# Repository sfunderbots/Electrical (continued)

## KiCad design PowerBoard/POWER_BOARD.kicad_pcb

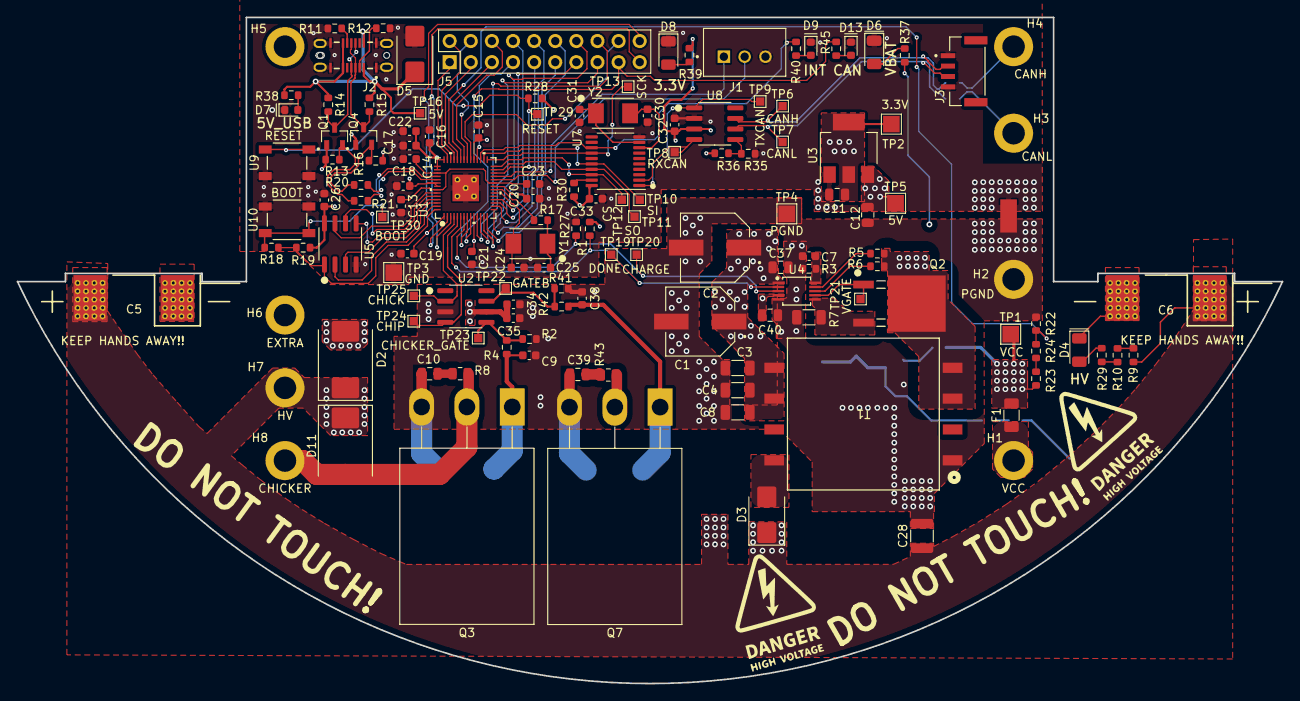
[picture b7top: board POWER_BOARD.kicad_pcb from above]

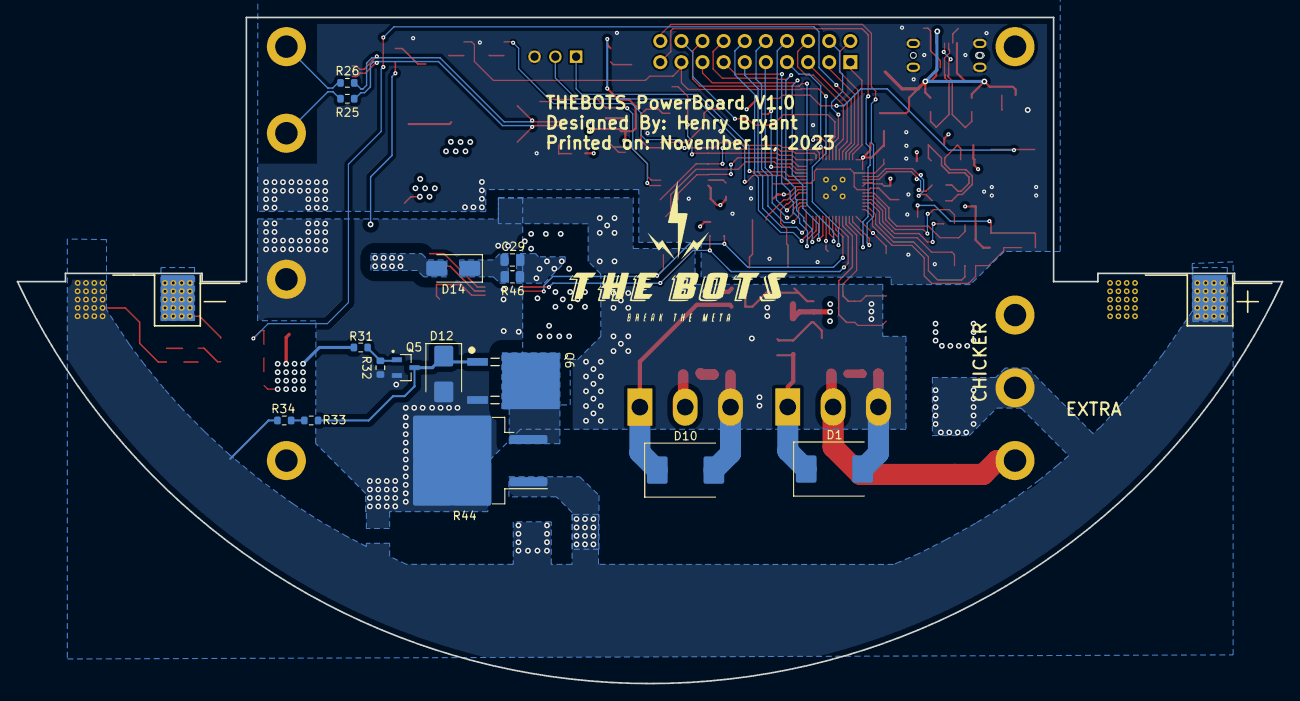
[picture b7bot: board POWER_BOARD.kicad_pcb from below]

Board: 4 copper layers, 152.1 x 80.1 mm, 154 parts (15 on the bottom side), 99 nets.

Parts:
C1, C2: 25SVPF100M; CAP_25SVPF100M
C3, C4, C8: C_22u_1206; C_1206_3216Metric
C5: 1000u; CP_Radial_Horizontal_D25.4mm_H45mm
C6: 1000u; CP_Radial_Horizontal_D25.4mm_H45mm_reversed
C7: 100p; C_0603_1608Metric
C9, C13, C14, C15, C16, C17, C18, C19, C20, C21, C26, C32, C33, C34, C38: 0.1u; C_0603_1608Metric
C10, C39: 1500p; C_0805_2012Metric
C11, C12: 10u; C_0805_2012Metric
C22, C23, C35: 1u; C_0603_1608Metric
C24, C25: 27p; C_0603_1608Metric
C28: 0.1u_600V; C_1210_3225Metric
C29: ?; C_0805_2012Metric
C30, C31: 22p; C_0603_1608Metric
C37, C40: C_10u; C_0805_2012Metric
D1, D10: SMCJ14A; D_SMC
D2, D11: MUR860J; D_SMC
D3: 2A 600V; D_SMB
D4: LED_red; LED_1206_3216Metric
D5: B220; D_SMB
D6, D8: LED; LED_1206_3216Metric
D7, D9, D13: LED; LED_0603_1608Metric
D12: 3SMBJ5929B-TP; D_SMB
D14: ?; D_SMA
F1: Fuse_0501010.WR; Fuse_1206_3216Metric
H1: VCC; MountingHole_2.7mm_M2.5_DIN965_Pad
H2: PGND; MountingHole_2.7mm_M2.5_DIN965_Pad
H3: CANL; MountingHole_2.7mm_M2.5_DIN965_Pad
H4: CANH; MountingHole_2.7mm_M2.5_DIN965_Pad
H5: 5V; MountingHole_2.7mm_M2.5_DIN965_Pad
H6: EXTRA; MountingHole_2.7mm_M2.5_DIN965_Pad
H7: HV; MountingHole_2.7mm_M2.5_DIN965_Pad
H8: CHICKER; MountingHole_2.7mm_M2.5_DIN965_Pad
J1: JST_B3B-XH-A
J2: USB4145-03-0170-C_REVA2; GCT_USB4145-03-0170-C_REVA2
J3: JST_BM04B-GHS-TBT
J5: Conn_02x10_Counter_Clockwise; PinHeader_2x10_P2.54mm_Vertical
NT1: NetTie_2; NetTie-2_SMD_Pad2.0mm
Q1, Q4: BSS138; SOT95P240X111-3N
Q2: FDD86250-F085; DPAK-3_ONS
Q3, Q7: FGH50T65SQD-F155; TO-247-3_Horizontal_TabDown
Q5: TN2130K1-G; SOT95P240X111-3N
Q6: STD11N60DM2; DPAK-3_ONS
R1, R9, R10, R27, R29, R32: 100k; R_0603_1608Metric
R2, R13, R14, R15, R16, R19, R28, R30, R41: 10k; R_0603_1608Metric
R3: 2.49k; R_0603_1608Metric
R4, R42: 110; R_0603_1608Metric
R5: 48.1k; R_0603_1608Metric
R6: 34.3k; R_0603_1608Metric
R7: 8m; R_1206_3216Metric
R8, R43: 2; R_0805_2012Metric
R11, R12, R35, R36: 5.1k; R_0603_1608Metric
R17, R18: 1k; R_0603_1608Metric
R20, R21: 27.4; R_0603_1608Metric
R22: R_200k; R_0603_1608Metric
R23, R24: R_470k; R_0603_1608Metric
R25, R26: R_0OHM_JUMPER; R_0603_1608Metric
R31: 270k; R_0603_1608Metric
R33, R34: 5.1M; R_0603_1608Metric
R37: 3k; R_0603_1608Metric
R38, R39, R40, R45: 330; R_0603_1608Metric
R44: 1k 50W; TO-263-2
R46: ?; R_0805_2012Metric
T1: 750032050; SMT_32050_WRE
TP1: VCC; TestPoint_Pad_2.0x2.0mm
TP2: 3.3V; TestPoint_Pad_2.0x2.0mm
TP3: GND; TestPoint_Pad_2.0x2.0mm
TP4: PGND; TestPoint_Pad_2.0x2.0mm
TP5: 5V; TestPoint_Pad_2.0x2.0mm
TP6: CANH; TestPoint_Pad_1.0x1.0mm
TP7: CANL; TestPoint_Pad_1.0x1.0mm
TP8: RXCAN; TestPoint_Pad_1.0x1.0mm
TP9: TXCAN; TestPoint_Pad_1.0x1.0mm
TP10: SI; TestPoint_Pad_1.0x1.0mm
TP11: SO; TestPoint_Pad_1.0x1.0mm
TP12: CS; TestPoint_Pad_1.0x1.0mm
TP13: SCK; TestPoint_Pad_1.0x1.0mm
TP16: 5V; TestPoint_Pad_1.0x1.0mm
TP19: DONE; TestPoint_Pad_1.0x1.0mm
TP20: CHARGE; TestPoint_Pad_1.0x1.0mm
TP21: VGATE; TestPoint_Pad_1.0x1.0mm
TP22: GATEB; TestPoint_Pad_1.0x1.0mm
TP23: CHICKER_GATE; TestPoint_Pad_1.0x1.0mm
TP24: CHIP; TestPoint_Pad_1.0x1.0mm
TP25: CHICK; TestPoint_Pad_1.0x1.0mm
TP29: RESET; TestPoint_Pad_1.0x1.0mm
TP30: BOOT; TestPoint_Pad_1.0x1.0mm
U1: RPI2040; QFN56_7X7_RPI
U2: MCP14A0454-E/SN; SOIC-8_3.9x4.9mm_P1.27mm
U3: AP2114HA-3.3TRG1; SOT-223-3_TabPin2
U4: LT3750; MSOP-10_3x3mm_P0.5mm
U5: W25Q16JVSNIQ; SOIC-8_3.9x4.9mm_P1.27mm
U7: MCP2515-xST; TSSOP-20_4.4x6.5mm_P0.65mm
U8: MCP2551-I-SN; SOIC-8_3.9x4.9mm_P1.27mm
U9, U10: PTS647SM38SMTR2LFS; SW_PTS647SM38SMTR2LFS_CNK
Y1: ABM3-12.000MHZ-D2Y-T; ABM3
Y2: ABM3-8.000MHZ-D2Y-T; ABM3

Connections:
5V_USB: D5.1 (K), J2.A4 (VBUS_A), J2.A9 (VBUS_A), J2.B4 (VBUS_B), J2.B9 (VBUS_B), R14.1, R15.1, R38.2, TP16.1
+3.3V: C11.1, C15.1, C16.1, C17.1, C18.1, C19.1, C20.1, C21.1, C22.1, C26.1, C32.1, C33.1, Q1.1, Q4.1, R1.2, R13.1, R16.1, R19.2, R28.1, R30.1, R36.1, R39.2, TP2.1, U1.1 (IOVDD), U1.10 (IOVDD), U1.22 (IOVDD), U1.33 (IOVDD), U1.42 (IOVDD), U1.43 (ADC_AVDD), U1.44 (VREG_VIN), U1.48 (USB_VDD), U1.49 (IOVDD), U3.2 (OUTPUT), U5.8 (VCC), U7.20 (VDD), U8.3 (VDD)
+5V: C12.1, H5.1, TP5.1, U3.3 (INPUT)
/Flyback_HV/AD_50W: Q6.2 (D), R44.3
/Flyback_HV/AD_G: D12.1 (K), Q5.3, Q6.1 (G), R33.2
/Flyback_HV/AD_LV_G: Q5.1, R31.2, R32.1
/Flyback_HV/AD_R: R33.1, R34.2
/Flyback_HV/CHICKER_GATE: R2.1, R4.2, TP23.1, U2.5 (OUTA)
/Flyback_HV/EXTRA_GATE: R41.1, R42.2, TP22.1, U2.7 (OUTB)
/Flyback_HV/HV_DIO: D3.2 (A), T1.8 (Vout)
/Flyback_HV/IGBTGATE_CHICKER: C9.1, D1.1 (K), Q3.1 (G), R4.1
/Flyback_HV/IGBTGATE_EXTRA: C38.1, D10.1 (K), Q7.1 (G), R42.1
/Flyback_HV/Q2D: D14.2 (A), Q2.2 (D), R5.2, R6.2, T1.3 (VinCOM2), T1.4 (VinCOM3)
/Flyback_HV/RBG: C7.1, R3.2, U4.10 (RBG)
/Flyback_HV/RCD: C29.2, D14.1 (K), R46.2
/Flyback_HV/RDCM: R6.1, U4.8 (RDCM)
/Flyback_HV/RVOUT: R5.1, U4.9 (RVOUT)
/Flyback_HV/SNUB: C39.1, R43.2
/Flyback_HV/SNUB2: C10.1, R8.2
/Flyback_HV/VSOURCE: Q2.3 (S), R7.2, U4.6 (SOURCE)
/Power/3V3_DIO: D8.2 (A), R39.1
/Power/CANR+: H4.1, R26.1
/Power/CANR-: H3.1, R25.1
/Power/USB_DIO: D7.2 (A), R38.1
/Power/VCC_DIO: D6.2 (A), R37.1
/Power/VCC_FUSE: F1.1, H1.1
/RP2040_CAN_FLASH/+1.1V: C13.1, C14.1, C23.1, U1.23 (DVDD), U1.45 (VREG_VOUT), U1.50 (DVDD)
/RP2040_CAN_FLASH/BOOT: R18.1, TP30.1, U10.1, U10.2
/RP2040_CAN_FLASH/CC1: J2.A5 (CC1), R12.1
/RP2040_CAN_FLASH/CC2: J2.B5 (CC2), R11.1
/RP2040_CAN_FLASH/D+: Q4.2, R16.2, R20.2
/RP2040_CAN_FLASH/D-: Q1.2, R13.2, R21.2
/RP2040_CAN_FLASH/DR+: R20.1, U1.47 (USB_DP)
/RP2040_CAN_FLASH/DR-: R21.1, U1.46 (USB_DM)
/RP2040_CAN_FLASH/Data+: J2.A6 (DP1), J2.B6 (DP2), Q4.3, R15.2
/RP2040_CAN_FLASH/Data-: J2.A7 (DN1), J2.B7 (DN2), Q1.3, R14.2
/RP2040_CAN_FLASH/GPIO6: J5.17, R45.1, U1.8 (GPIO6)
/RP2040_CAN_FLASH/GPIO7: J5.16, U1.9 (GPIO7)
/RP2040_CAN_FLASH/GPIO8: J5.15, U1.11 (GPIO8)
/RP2040_CAN_FLASH/GPIO9: J5.14, U1.12 (GPIO9)
/RP2040_CAN_FLASH/GPIO10: J5.13, U1.13 (GPIO10)
/RP2040_CAN_FLASH/GPIO11: J5.12, U1.14 (GPIO11)
/RP2040_CAN_FLASH/GPIO12: J5.11, U1.15 (GPIO12)
/RP2040_CAN_FLASH/GPIO13: J5.10, U1.16 (GPIO13)
/RP2040_CAN_FLASH/GPIO14: J5.9, U1.17 (GPIO14)
/RP2040_CAN_FLASH/GPIO15: J5.8, U1.18 (GPIO15)
/RP2040_CAN_FLASH/GPIO21: J5.7, U1.32 (GPIO21)
/RP2040_CAN_FLASH/GPIO22: J5.18, U1.34 (GPIO22)
/RP2040_CAN_FLASH/GPIO23: J5.4, U1.35 (GPIO23)
/RP2040_CAN_FLASH/GPIO24: J5.6, U1.36 (GPIO24)
/RP2040_CAN_FLASH/GPIO25: J5.5, U1.37 (GPIO25)
/RP2040_CAN_FLASH/GPIO27_ADC1: J5.3, U1.39 (GPIO27/ADC1)
/RP2040_CAN_FLASH/GPIO28_ADC2: J5.2, U1.40 (GPIO28/ADC2)
/RP2040_CAN_FLASH/GPIO29_ADC3: J5.1, U1.41 (GPIO29/ADC3)
/RP2040_CAN_FLASH/INT: R40.1, U1.31 (GPIO20), U7.13 (~INT)
/RP2040_CAN_FLASH/OSC1: C31.1, U7.9 (OSC1), Y2.1
/RP2040_CAN_FLASH/OSC2: C30.1, U7.8 (OSC2), Y2.2
/RP2040_CAN_FLASH/QSPI_SCLK: U1.52 (SQPI_SCLK), U5.6 (CLK)
/RP2040_CAN_FLASH/QSPI_SD0: U1.53 (SQPI_SD0), U5.5 (DI(IO0))
/RP2040_CAN_FLASH/QSPI_SD1: U1.55 (SQPI_SD1), U5.2 (DO(IO1))
/RP2040_CAN_FLASH/QSPI_SD2: U1.54 (SQPI_SD2), U5.3 (IO2)
/RP2040_CAN_FLASH/QSPI_SD3: U1.51 (SQPI_SD3), U5.7 (IO3)
/RP2040_CAN_FLASH/QSPI_SS: R18.2, R19.1, U1.56 (SQPI_SS_N), U5.1 (~CS)
/RP2040_CAN_FLASH/RUN: R28.2, TP29.1, U1.26 (RUN), U9.1, U9.2
/RP2040_CAN_FLASH/RX: J5.20, U1.2 (GPIO0)
/RP2040_CAN_FLASH/RXCAN: TP8.1, U7.2 (RXCAN), U8.4 (RXD)
/RP2040_CAN_FLASH/SPI0_CS: TP12.1, U1.28 (GPIO17), U7.18 (~CS)
/RP2040_CAN_FLASH/SPI0_RX: TP11.1, U1.27 (GPIO16), U7.17 (SO)
/RP2040_CAN_FLASH/SPI0_SCK: TP13.1, U1.29 (GPIO18), U7.14 (SCK)
/RP2040_CAN_FLASH/SPI0_TX: TP10.1, U1.30 (GPIO19), U7.16 (SI)
/RP2040_CAN_FLASH/SWCLK: J1.2, U1.24 (SWCLK)
/RP2040_CAN_FLASH/SWDIO: J1.1, U1.25 (SWDIO)
/RP2040_CAN_FLASH/TX: J5.19, U1.3 (GPIO1)
/RP2040_CAN_FLASH/TXCAN: TP9.1, U7.1 (TXCAN), U8.1 (TXD)
/RP2040_CAN_FLASH/Vref1.65V: R35.1, R36.2, U8.5 (Vref)
/RP2040_CAN_FLASH/XIN: C24.2, U1.20 (XIN), Y1.2
/RP2040_CAN_FLASH/XOUT: R17.2, U1.21 (XOUT)
BATT_LEVEL: R22.1, R24.2, U1.38 (GPIO26/ADC0)
CAN+: J3.2, R26.2, TP6.1, U8.7 (CANH)
CAN-: J3.3, R25.2, TP7.1, U8.6 (CANL)
CHARGE: R27.1, TP20.1, U1.7 (GPIO5), U4.3 (CHARGE)
CHICKER: TP25.1, U1.4 (GPIO2), U2.2 (INA)
CHICKER_HV: D11.2 (A), H8.1, Q3.2 (C), R8.1
CHIP_EXTRA: TP24.1, U1.5 (GPIO3), U2.4 (INB)
DONE: R1.1, TP19.1, U1.6 (GPIO4), U4.2 (~DONE)
EXTRA_HV: D2.2 (A), H6.1, Q7.2 (C), R43.1
GND: C11.2, C13.2, C14.2, C15.2, C16.2, C17.2, C18.2, C19.2, C20.2, C21.2, C22.2, C23.2, C24.1, C25.1, C26.2, C30.2, C31.2, C32.2, C33.2, D5.2 (A), D6.1 (K), D7.1 (K), D8.1 (K), D9.1 (K), D13.1 (K), J1.3, J2.A1 (GND_A), J2.A12 (GND_A), J2.B1 (GND_B), J2.B12 (GND_B), J2.S1 (SHIELD), J2.S2 (SHIELD), J2.S3 (SHIELD), J2.S4 (SHIELD), J3.1, J3.4, NT1.2, R11.2, R12.2, R27.2, R35.2, TP3.1, U1.19 (TESTEN), U1.57 (GND), U3.1 (GND), U5.4 (GND), U7.10 (VSS), U8.2 (VSS), U9.3, U9.4, U10.3, U10.4
GNDPWR: C1.2, C2.2, C3.2, C4.2, C5.2, C6.2, C7.2, C8.2, C9.2, C10.2, C12.2, C28.2, C34.2, C35.2, C37.2, C38.2, C39.2, C40.2, D1.2 (A), D4.1 (K), D10.2 (A), D12.2 (A), H2.1, NT1.1, Q3.3 (E), Q5.2, Q6.3 (S), Q7.3 (E), R2.2, R3.1, R7.1, R22.2, R32.2, R41.2, R44.2, T1.1 (VoutCOM), TP4.1, U2.3 (GND), U4.5 (GND)
HV: C5.1, C6.1, C28.1, D2.1 (K), D3.1 (K), D11.1 (K), H7.1, R9.2, R34.1, R44.1
unnamed: C25.2, R17.1, Y1.1
unnamed: D4.2 (A), R29.1
unnamed: D9.2 (A), R40.2
unnamed: D13.2 (A), R45.2
unnamed: Q2.1 (G), TP21.1, U4.7 (GATE)
unnamed: R10.1, R29.2
unnamed: R9.1, R10.2
unnamed: R23.2, R24.1
unnamed: R30.2, U7.19 (~RESET)
VCC: C1.1, C2.1, C3.1, C4.1, C8.1, C29.1, C34.1, C35.1, C37.1, C40.1, F1.2, R23.1, R31.1, R37.2, R46.1, T1.5 (Vin1), T1.6 (Vin2), TP1.1, U2.6 (VDD), U4.1 (VTRANS), U4.4 (VCC)

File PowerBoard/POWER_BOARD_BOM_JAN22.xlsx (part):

Reference | Value | Footprint | JLC Extended | MPN | JLC Part # | Digikey cost 1 unit | Digikey Cost 10 units | JLC Cost | Layer | DNP QTY | Qty per board | QTY after DNP | QTY Have | QTY need if Digikey | QTY digikey order | QTY to solder digikey | QTY *10 + spare for JLC | Digikey Cost (total) | JLC Cost with Extended part fee (total) | Override | Lowest Cost (Digikey vs JLC)
C1, C2 | 25SVPF100M | bots:CAP_25SVPF100M | yes | 25SVPF100M | C136279 | 1.97000 | 1.4710000000000001 | 1.0630500000000001 |  |  | 2 | 2 |  | 20 | 0 | 0 | 20 | 29.42 | 25.301000000000002 |  | 25.301000000000002 | JLC
C3, C4, C8 | 22u_1206 | bots:C_1206_3216Metric | no | CL31A226KAHNNNE | C12891 | 0.51000 | 0.33800000000000002 | 6.4500000000000002E-2 |  |  | 3 | 3 |  | 30 | 0 | 24 | 30 | 10.14 | 1.9350000000000001 |  | 1.9350000000000001 | JLC
C5, C6 | 1000u | bots:CP_Radial_Horizontal_D25.4mm_H45mm |  | ESMQ251VSN102MQ45S |  | 8.76000 | 7.53 |  |  |  | 2 | 2 | 8 | 8 | 8 | 16 | 12 | 70.08 | EMPTY |  | 70.08 | DIGIKEY
C7 | 100p | bots:C_0603_1608Metric | no | CL10C101JB8NNNC | C14858 | 0.14000 | 3.6999999999999998E-2 | 2.5999999999999999E-3 |  |  | 1 | 1 |  | 10 | 0 | 8 | 10 | 0.37 | 2.5999999999999999E-2 |  | 2.5999999999999999E-2 | JLC
C9, C13-C21, C26, C32-C34, C38 | 0.1u | bots:C_0603_1608Metric | no | CC0603KRX7R9BB104 | C14663 | 0.14000 | 3.2599999999999997E-2 | 2.0999999999999999E-3 |  |  | 15 | 15 |  | 150 | 0 | 120 | 150 | 4.8899999999999997 | 0.315 |  | 0.315 | JLC
C10, C39 | 1500p | bots:C_0805_2012Metric | yes | C2012C0G2A152JT000N | C342996 | 0.23000 | 0.156 | 3.9600000000000003E-2 |  | 1 | 2 | 1 |  | 10 | 10 | 8 | 10 | 1.56 | 4.4359999999999999 |  | 1.56 | DIGIKEY
C11, C12, C37, C40 | 10u | bots:C_0805_2012Metric | no | GRM21BR61H106KE43L | C440198 | 0.48000 | 0.317 | 6.4500000000000002E-2 |  |  | 4 | 4 |  | 40 | 0 | 32 | 40 | 12.68 | 2.58 |  | 2.58 | JLC
C22, C23, C35 | 1u | bots:C_0603_1608Metric | no | CL10A105KB8NNNC | C15849 | 0.20000 | 0.13200000000000001 | 4.5999999999999999E-3 |  |  | 3 | 3 |  | 30 | 0 | 24 | 30 | 3.96 | 0.13800000000000001 |  | 0.13800000000000001 | JLC
C24, C25 | 27p | bots:C_0603_1608Metric | no | CC0603JRNPO9BN270 | C107045 | 0.14000 | 4.7E-2 | 2.7000000000000001E-3 |  |  | 2 | 2 |  | 20 | 0 | 16 | 20 | 0.94 | 5.4000000000000006E-2 |  | 5.4000000000000006E-2 | JLC
C27 | 0.22u_0805 | bots:C_0805_2012Metric | no | CL21B224KBFNNNE | C5378 | 0.14000 | 6.4000000000000001E-2 | 1.03E-2 | Bottom |  | 1 | 1 |  | 10 | 10 | 8 | 10 | 0.64 | 0.10300000000000001 |  | 0.64 | DIGIKEY
C28 | 0.1u_600V | bots:C_1210_3225Metric | yes | C1210C104KBRAC7800 | C2902776 | 0.61 | 0.40799999999999997 | 0.36230000000000001 |  |  | 1 | 1 |  | 10 | 10 | 8 | 10 | 4.08 | 7.6630000000000003 |  | 4.08 | DIGIKEY
C30, C31 | 22p | bots:C_0603_1608Metric | no | CL10C220JB8NNNC | C1653 | 0.14000 | 5.8000000000000003E-2 | 5.1999999999999998E-3 |  |  | 2 | 2 |  | 20 | 0 | 16 | 20 | 1.1600000000000001 | 0.104 |  | 0.104 | JLC
D1, D10 | SMCJ15A | bots:D_SMC | yes | SMCJ15A | C438099 | 0.62 | 0.53400000000000003 | 7.5300000000000006E-2 | Bottom | 1 | 2 | 1 |  | 8 | 8 | 8 | 10 | 4.96 | 4.7930000000000001 |  | 4.96 | DIGIKEY
D2, D11 | MUR860J | bots:D_SMC | yes | MUR860J | C169513 | 0.74000 | 0.623 | 6.5600000000000006E-2 |  | 1 | 2 | 1 |  | 8 | 8 | 8 | 10 | 5.92 | 4.6959999999999997 | DIGIKEY | 5.92 | DIGIKEY
D3 | 2A 600V | bots:D_SMB | yes | MURS160-E3/52T | C59627 | 0.68000 | 0.53 | 0.1038 |  |  | 1 | 1 |  | 10 | 0 | 8 | 10 | 5.3000000000000007 | 5.0780000000000003 |  | 5.0780000000000003 | JLC
D4 | LED_red | bots:LED_0805_2012Metric | no | NCD0805R1 | C84256 | 0.39 | 0.216 | 1.2200000000000001E-2 |  |  | 1 | 1 |  | 10 | 0 | 8 | 10 | 2.16 | 0.12200000000000001 |  | 0.12200000000000001 | JLC
D5 | B220 | bots:D_SMB | yes | B220-13-F | C110480 | 0.68000 | 0.47399999999999998 | 8.3299999999999999E-2 |  | 1 | 1 | 0 |  | 0 | 0 | 0 | 0 | 0 | 4.04 |  | 0 | DIGIKEY
D6, D8, D15 | LED | bots:LED_0805_2012Metric | no | KT-0805G | C2297 | 0.39 | 0.216 | 1.2699999999999999E-2 |  |  | 3 | 3 |  | 30 | 0 | 24 | 30 | 6.4799999999999995 | 0.38100000000000001 |  | 0.38100000000000001 | JLC
D7 | LED_blue | bots:LED_0603_1608Metric | no | KT-0603W | C2290 | 0.39 | 0.20100000000000001 | 9.5999999999999992E-3 |  |  | 1 | 1 |  | 10 | 0 | 8 | 10 | 2.0100000000000002 | 9.5999999999999988E-2 |  | 9.5999999999999988E-2 | JLC
D9, D13 | LED | bots:LED_0603_1608Metric | no | 19-213/Y2C-CQ2R2L/3T(CY) | C72038 | 0.39 | 0.20100000000000001 | 1.95E-2 |  |  | 2 | 2 |  | 20 | 0 | 16 | 20 | 4.0200000000000005 | 0.39 |  | 0.39 | JLC
D12 | 3SMBJ5929B-TP | bots:D_SMB |  | 3SMBJ5929B-TP | N/A | 0.61000 | 0.436 | 0.63 | Bottom |  | 1 | 1 |  | 10 | 10 | 8 | 10 | 4.3600000000000003 | EMPTY |  | 4.3600000000000003 | DIGIKEY
D14 | US1M | bots:D_SMA | no | US1M | C412437 | 0.17 | 0.122 | 0.1038 | Bottom |  | 1 | 1 |  | 10 | 10 | 8 | 10 | 1.22 | 1.038 |  | 1.22 | DIGIKEY
F1 | 0501015.WR1 | bots:Fuse_1206_3216Metric | yes | 0501015.WR1 | C410346 | 1.54 | 1.4 | 9.9199999999999997E-2 |  |  | 1 | 1 |  | 8 | 0 | 8 | 10 | 12.32 | 5.032 |  | 5.032 | JLC
J1 | JST_B3B-XH-A | bots:JST_B3B-XH-A |  | B3B-XH-A(LF)(SN) |  | 0.30000 | 0.23200000000000001 | 0.31 |  | 1 | 1 | 0 |  | 0 | 0 | 0 | 0 | 0 | EMPTY |  | 0 | DIGIKEY
J2 | USB4145-03-0170-C_REVA2 | bots:GCT_USB4145-03-0170-C_REVA2 |  | USB4145-03-0170-C |  | 1.56000 | 1.3140000000000001 | 1.61 |  | 1 | 1 | 0 |  | 0 | 0 | 0 | 0 | 0 | EMPTY |  | 0 | DIGIKEY
J3 | JST_BM04B-GHS-TBT | bots:JST_BM04B-GHS-TBT |  | BM04B-GHS-TBT |  | 0.71000 | 0.60599999999999998 | 0.31 |  | 1 | 1 | 0 |  | 0 | 0 | 0 | 0 | 0 | EMPTY |  | 0 | DIGIKEY
J5 | Conn_02x10_Counter_Clockwise | bots:PinHeader_2x10_P2.54mm_Vertical |  | PH2-20-UA |  | 0.37000 | 0.30599999999999999 |  |  | 1 | 1 | 0 |  | 0 | 0 | 0 | 0 | 0 | EMPTY |  | 0 | DIGIKEY
Q1, Q4 | BSS138 | bots:SOT95P240X111-3N | no | BSS138 | C7420339 | 0.5 | 0.22500000000000001 | 1.2800000000000001E-2 |  |  | 2 | 2 |  | 20 | 0 | 16 | 20 | 4.5 | 0.25600000000000001 |  | 0.25600000000000001 | JLC
Q2 | IRFR3410TRPBF | bots:DPAK-3_ONS | yes | IRFR3410TRPBF | C605020 | 1.44000 | 1.17 | 0.46500000000000002 |  |  | 1 | 1 |  | 8 | 0 | 8 | 10 | 11.52 | 8.6900000000000013 |  | 8.6900000000000013 | JLC
Q3, Q7 | FGH50T65SQD-F155 | bots:TO-247-3_Horizontal_TabDown | yes | FGH50T65SQD-F155 | C132704 | 6.22000 | 6.22 | 4.0393999999999997 |  | 1 | 2 | 1 |  | 8 | 8 | 8 | 10 | 49.76 | 44.433999999999997 | DIGIKEY | 49.76 | DIGIKEY
Q5 | TN2130K1-G | bots:SOT95P240X111-3N |  | TN2130K1-G | C626652 | 0.65000 | 0.65 |  | Bottom |  | 1 | 1 |  | 8 | 8 | 8 | 10 | 5.2 | EMPTY |  | 5.2 | DIGIKEY
Q6 | IPD60R3K4CEAUMA1 | bots:DPAK-3_ONS |  | IPD60R3K4CEAUMA1 |  | 0.76000 | 0.65300000000000002 |  | Bottom |  | 1 | 1 |  | 8 | 8 | 8 | 10 | 6.08 | EMPTY |  | 6.08 | DIGIKEY
R1, R9, R10, R27, R29 | 100k | bots:R_0603_1608Metric | no | 0603WAF1003T5E | C25803 | 0.15 | 2.3E-2 | 8.9999999999999998E-4 |  |  | 5 | 5 |  | 50 | 0 | 40 | 50 | 1.1499999999999999 | 4.4999999999999998E-2 |  | 4.4999999999999998E-2 | JLC
R32 | 100k | bots:R_0603_1608Metric | no | 0603WAF1003T5E | C25803 | 0.15 | 2.3E-2 | 8.9999999999999998E-4 | Bottom |  | 1 | 1 |  | 10 | 10 | 8 | 10 | 0.22999999999999998 | 8.9999999999999993E-3 |  | 0.22999999999999998 | DIGIKEY
R2, R13-R16, R19, R28, R30, R41 | 10k | bots:R_0603_1608Metric | no | 0603WAF1002T5E | C25804 | 0.15 | 2.3E-2 | 8.0000000000000004E-4 |  |  | 9 | 9 |  | 90 | 0 | 72 | 90 | 2.0699999999999998 | 7.2000000000000008E-2 |  | 7.2000000000000008E-2 | JLC
R3 | 2.49k | bots:R_0603_1608Metric |  | RMCF0603FT2K49 | C108190 | 0.15 | 2.3E-2 | 1E-3 |  |  | 1 | 1 |  | 10 | 10 | 8 | 10 | 0.22999999999999998 | EMPTY |  | 0.22999999999999998 | DIGIKEY
R4, R42 | 120R | bots:R_0603_1608Metric | no | 0603WAF1200T5E | C22787 | 0.15 | 2.3E-2 | 1E-3 |  |  | 2 | 2 |  | 20 | 0 | 16 | 20 | 0.45999999999999996 | 0.02 |  | 0.02 | JLC
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
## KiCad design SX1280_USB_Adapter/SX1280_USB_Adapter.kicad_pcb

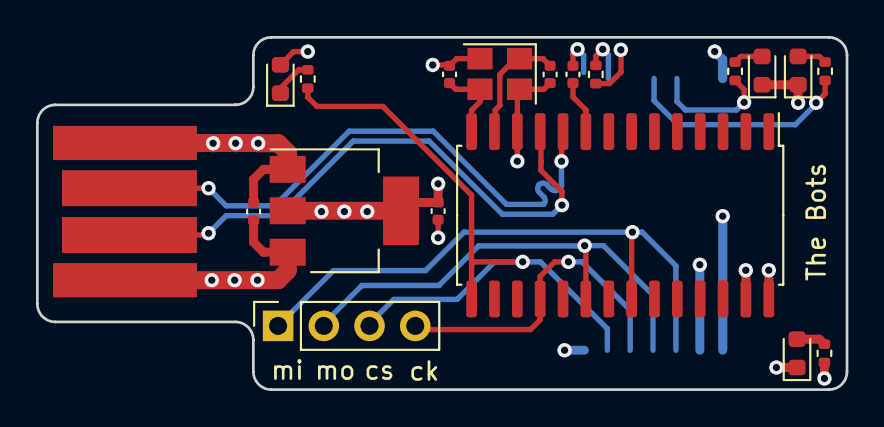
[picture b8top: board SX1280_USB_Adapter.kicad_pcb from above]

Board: 4 copper layers, 45.0 x 19.6 mm, 20 parts (1 on the bottom side), 19 nets.

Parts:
C1, C4: 20p; C_0402_1005Metric
C2, C5: 104; C_0402_1005Metric
C3: 47p2; C_0402_1005Metric
D1, D2, D3, D4: LED; LED_0603_1608Metric
J1: USB_A_PLUG; USB_PCB
J2: Conn_01x04_Female; PinSocket_1x04_P2.54mm_Vertical
R2, R3, R4, R6: R330; R_0402_1005Metric
R5: 1k; R_0402_1005Metric
U1: AMS1117-3.3; SOT-223-3_TabPin2
U2: CH341a; SOIC-28W_7.5x17.9mm_P1.27mm
U3: SX1280; E28-2G4M12S-SX1280
Y1: Crystal_GND24; Crystal_SMD_3225-4Pin_3.2x2.5mm

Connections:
/3V3: C5.2, D4.2 (A), R5.1, U1.2 (VO), U3.1 (VCC)
/5V: C2.2, J1.1 (VBUS), R2.1, U1.3 (VI), U2.28 (VCC)
/CLK: J2.4, U2.18 (~DCD/D3/DCK), U3.5 (SCK)
/CS: J2.3, R3.2, U2.15 (~CTS/D0/CS0), U3.6 (NSS)
/GND: C1.1, C2.1, C3.1, C4.1, C5.1, D1.1 (K), D2.1 (K), D3.1 (K), J1.4 (GND), U1.1 (GND), U2.12 (GND), U2.27 (~TEN/BUSY/WAIT), U3.2 (GND), U3.7 (GND), U3.8 (GND), U3.14 (GND), Y1.2, Y1.4
/MISO: J2.1, U2.22 (~SLP/D7/DIN), U3.3 (MISO)
/MOSI: J2.2, U2.20 (~DTR/D5/DOUT), U3.4 (MOSI)
/USB D+: J1.3 (D+), U2.10 (UD+)
/USB D-: J1.2 (D-), U2.11 (UD-)
unnamed: D1.2 (A), R2.2
unnamed: D2.2 (A), R4.2
unnamed: D3.2 (A), R6.2
unnamed: D4.1 (K), R3.1
unnamed: C3.2, U2.9 (V3)
unnamed: C1.2, U2.13 (XI), Y1.1
unnamed: C4.2, U2.14 (XO), Y1.3
unnamed: R4.1, U3.11 (DIO1)
unnamed: R6.1, U3.12 (DIO2)
unnamed: R5.2, U3.9 (nReset)

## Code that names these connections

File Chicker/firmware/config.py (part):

# Chicker firmware v2 - every constant in one place. No logic lives in this file.
#
# Provenance tags:
#   [SCH]   KiCad schematic            [DS]    component datasheet
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# ---------------------------------------------------------------------------
PIN_CHIP = 2            # chip IGBT gate driver - never fired, held low
PIN_KICK = 3            # kick IGBT gate driver
PIN_DONE = 4            # LT3750 DONE (open collector: high = charging)
PIN_CHARGE = 5          # LT3750 CHARGE (rising edge starts a cycle)
PIN_CAN_LED = 6
PIN_NOT_DISCHARGE = 8   # ~DISCHARGE: low = dump bank into the 1k resistors
PIN_SHELL_OFF = 9       # reed switch (digital for now, analog version in to-test/)
PIN_CAN_INT = 20
PIN_BREAKBEAM = 23
PIN_ADC_BATT = 26
PIN_ADC_5V = 27
PIN_ADC_HV = 29

# Pin the kick PIO program drives. Set to PIN_CAN_LED for an LED dry run:
# the real KICK pin is then held low as a plain GPIO.
KICK_OUTPUT_PIN = PIN_KICK
KICK_PIO_SM = 0          # PIO0 state machine 0
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
# ---------------------------------------------------------------------------
# Charge state machine (Henry's charge chart; docs/CHARGE-STATE-MACHINE-REVIEW.md)
# Every charge decision is made on timers and the DONE pin, never on the HV reading (review note N-0).
# "time since last chg" = time since CHARGE last went high (the start of the current charge cycle).
# ---------------------------------------------------------------------------
BATT_SETTLE_MS = 2000            # [RC26] "New Charge from Bat: Wait for 2s"
NEW_CHARGE_WAIT_MS = 50          # [RC26] "New Charge: Wait for 50ms" (CHARGE held low)
CHARGE_SPACING_MS = 500          # [Henry] GUARD "time since last chg >= 500ms" before every new cycle
CHARGE_START_CHECK_MS = 50       # [RC26] "Charge Toggle Wait: wait for 50ms", then check the DONE edge latch
CHARGE_TIMEOUT_MS = 4500         # [Henry] GUARD "time since last chg >= 4500ms": done still 1 = too slow
TOPOFF_PERIOD_MS = 5000          # [Henry] GUARD "time since last chg >= 5000ms": toggle CHARGE to top off
CHARGE_TOGGLE_LOW_MS = 50        # [RC26] "Charge Toggle": CHARGE low this long (datasheet needs 20 us)
SAFE_CHARGE = 0                  # [Henry] safe_chg branch: 1 = charge to ~50 V once, then Disabled (bench)
SAFE_CHARGE_MS = 236             # [Henry] GUARD "time since last chg >= 236ms" (~50 V)
SAFE_CHARGE_WAIT_MS = 5000       # [Henry] "Charged to ~50V: wait 5s"
OVERVOLT_V = 220.0               # [Henry] X-1: ANY STATE HV >= 220 V -> Disabled (full bank is 206-212 V)
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CAN_TX_ENABLED = True
CAN_LOOPBACK_SELFTEST = True
STATUS_PERIOD_MS = 50            # 20 Hz status to the Pi
STATUS_MIN_GAP_MS = 5            # extra status frames on changes, rate limited
CAN_SEND_REJECT_EVENTS = True    # [T-2, pending team] send a CMD_REJECTED event for a bad / unusable command

# Heartbeat (mode elements 3 and 4, note HB-1). The Pi sends one every 200 ms (5 Hz). Any valid frame from
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
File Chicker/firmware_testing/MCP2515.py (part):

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Com_RecBuff = [0, 0, 0, 0, 0, 0, 0, 0] #8
# data = 0

SPI0_RX = 16
SPI0_CS0 = 17
SPI0_SCK = 18
SPI0_TX = 19


# debug = False
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class MCP2515():
    def __init__(self):
		self.spi = SPI(0)
		self.spi = SPI(0,10000_000,polarity=0, phase=0,sck=Pin(SPI0_SCK),mosi=Pin(SPI0_TX),miso=Pin(SPI0_RX))
		self.cs = Pin(SPI0_CS0,Pin.OUT)
        
    def ReadByte(self, addr):
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
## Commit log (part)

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2023-12-07 component placement, first pass
2023-12-07 tracking footprints and 3D step
2023-12-07 relocated to align encoder with board geometric center
2023-12-08 MCU fanout, power stage roughed in, setup is now 6L
2023-12-09 output via stitching
2023-12-10 VCC / GND pours
2023-12-10 initial layout pass
2023-12-10 layout clean-up
2023-12-11 midplate mods
2023-12-11 initial DRC cleanup
2023-12-14 added PTH's for cap holders and shell
2023-12-16 redone layout
2023-12-26 midplate changes, ready for order
2023-12-27 midplate updates
2023-12-29 WIP Buck for Faceplate
2023-12-29 midplate 5V buck converter
2024-01-04 spaced out mounting points by 0.5mm
2024-01-05 initial layout
2024-01-05 project sync updates
2024-01-06 layout complete
2024-01-06 GND stitch update
2024-01-07 fixed hole clearance issues
2024-01-08 midplate v1 ready for review
2024-01-12 swapped pins around for CAN
2024-01-12 midplate update with different buck regulator pad size
2024-01-17 update to midplate and powerboard
2024-01-21 update to midplate hole placements
2024-01-24 power board and midplate updates (mostly finalized)
2024-01-25 discharge circuit changes
2024-01-26 BOM clean-up
2024-01-27 finalize connections
2024-01-27 Finalize faceplate
2024-01-27 Fix stuff up
2024-01-27 fix socket
2024-01-27 update radio model
2024-01-27 chicker v1.0 ordered
2024-01-27 step file
2024-01-27 midplate
2024-01-29 name change
2024-01-30 faceplate modifications
2024-01-30 finalize with 0ohms
2024-02-03 update to schematic but something on layout is broken
2024-02-03 branch
2024-02-03 netlist
2024-02-05 faceplate updates
2024-02-05 faceplate schematic
2024-02-07 add faceplate slit for camera cable
2024-02-07 midplate + chicker bom
2024-02-07 faceplate radio fixes
2024-02-08 midplate 4 layers, chicker shell off limit switch idea
2024-02-08 chicker discharge HV shell off fixed
    pull up to 3v3 and limit switch, input to RP2040, output to inverted discharge signal which discharges if it is set to 0
2024-02-11 chicker discharge circuit finalized
2024-02-11 chicker v1.1 changes
2024-02-17 Final touches
2024-02-18 Production files
2024-02-18 Ordered faceplate
2024-02-18 added a global library for symbols
2024-02-19 added basic firmware in micropython
2024-02-19 chicker firmware update
2024-02-19 update to firmware
2024-02-20 adding checks for DONE, if charge cycle started / completed properly
2024-02-20 firmware update
2024-02-21 firmware mostly done for testing HV
2024-02-23 chicker firmware mostly good, ready to test
2024-02-23 added safe charge mode in code
2024-02-23 accidental comments, setting everything to real values
2024-02-24 main
2024-02-26 chicker updates
2024-02-26 chicker v1.1 working
2024-02-27 chicker v1.1 updates
    nearly done, need to fix rules
2024-02-28 v1.1 mostly done, need to add tooling holes
2024-02-28 chicker v1.1 done (TM)
2024-02-28 midplate thoughts
2024-03-01 feat: add midplate and shell mounting
    - Reduce PCB Diameter to 174mm
    - Add cutouts for shell mounting
    - Reduce cap holder screw holes from 6 to 4
    - Rotate power switch 30 deg towards edge
    - Add holes for midplate mounting
2024-03-05 changed spacing
2024-03-10 firmware update
    trying to get ISR pulse generator working
2024-03-11 update motor mount footprints
2024-03-11 code is functionally ready to test
    after work tomorrow with an oscilloscope to figure out what is going on with the gate driver
2024-03-11 midplate updating to global symbol library
2024-03-11 midplate updates
    - pretty close to order: need to verify if we can get 2oz outer copper
2024-03-11 added files from RobertHH on github
    - https://github.com/robert-hh/RP2040-Examples/tree/master
2024-03-11 add engineer vector graphic
2024-03-11 update step files
2024-03-12 chicker + midplate changes
    -ready to order midplate
2024-03-12 midplate - with alt parts
2024-03-12 wip baseplate
2024-03-13 firmware update
    - weird bug causing startup cycle to start without command, variable is 0 all the time as far as im aware
2024-03-14 removed old midplate design for merge resolution
2024-03-14 mostly finished
2024-03-15 baseplate updates
2024-03-15 baseplate
2024-03-15 wip baseplate mostly done
2024-03-15 wip breakbeam voltage divider
2024-03-15 baseplate done
2024-03-17 trying to change frequency of pulse counter
    sad times broke an IGBT and a flyback diode and maybe another IGBT
    cant charge with solenoid plugged in at the moment, i plugged it in and it kicked immediately and thats likely why it broke or somehow
2024-03-19 firmware changed to running pulses at 8MHz
    pulses are very accurate, can go down to 1us at the minimum, likely 100us at the maximum
2024-03-21 firmware change
    - changed pulses to be running at a slower frequency (seems it is slightly inaccurate of creating the pulse)
    - added a check to not kick when charging (based on done signal), two gate driver chips were burned from a pulse train or even a single pulse, not sure, when charging from 0V
2024-03-27 code modified but currently buggy
    - when vcc repowered board it starts charge cycle right away instead of waiting
2024-03-31 chicker works! (slight bug in code, but works)
    - avoid kicking near when the next charge cycle starts (as it doesnt stop the pulse if a charge cycle starts after the pulse goes out). this will break the IGBT due to potential delays / and maybe cu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
2024-03-31 modified code to not charge for 50ms when kick issued
2024-04-04 chicker modifications (mostly ready to order)
2024-04-07 fixed most issues with JLC ordering
2024-04-10 Add edge cut suggestion for shell to User 8
2025-01-17 modified transmitter circuit
2025-05-19 ESD+schematic fixes
2025-05-26 chicker v1.1 basic parts
2025-05-27 more parts
2025-05-28 changed more to basic
2025-05-28 chicker v1.1 ordered!
2025-06-09 firmware + RCD snubber
2025-06-15 chicker firmware flash
2025-06-26 testing code
    havent made much progress
2025-07-12 changed transceiver for faceplate
    + removed caps on chicker can
2025-07-14 damping firmware
    damping firmware
2025-07-17 damping can bus code
    + changing charging to every 5s
2025-07-17 stuff
2025-07-18 changes but not done
    i think it works but need to change some stuff so charging is not in simulation mode
2025-07-18 testing
2025-07-18 reverted to old code
2025-07-18 modified chicker firmware
2025-07-18 reverting HV scaling
2025-07-20 test v1
2025-07-21 updated code hopefully works
2025-07-22 trying to fix
2025-07-23 reverted to old code
    ACTUALLY OLD CODE (ROBOCUP)
2025-07-23 idle to charge
    charge, to idle and back to charge WORKS! need to test kicking and possibly change reset logic for some reason it waits 2s before charging again???
2025-07-23 firmware update
    v2
2025-07-24 chicker code does not work.
2025-07-24 Update main.py
    - idle mode: doesnt discharge (weird?)
    - damping mode: discharges after switching from a charge state (aka done state read as high but shouldnt do this theoretically)
    - charge mode: works I think?
    - autokick mode: works I think?
2025-07-24 works minus damping code
2025-07-24 trying 2 fix damp code
2025-07-24 need to revert can led 4 bbeam
2025-07-24 proper values
2025-07-24 works!
2025-07-25 1kHz to 10kHz ideal for damping
    possibly wondering about discrepancy of not being able to damp at the same value maybe thats a timer thing or maybe its the array I used. possibly why were seeing kick speed variation. maybe need a n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
2025-07-26 damping
2025-08-04 chatgpt created this CAUTION
    - AKHIL - maybe you can integrate this version of the kick code and PWM better in my code instead of what is implemented currently for the KICK and DAMP functions?
    Henry
2025-12-31 pcb pin number change
    (from last summer)
2025-12-31 reed switch code
    very bare bones reed switch code
2026-01-01 elliptic integral
2026-01-01 modified code
2026-01-02 working code
2026-01-19 kicad rules
2026-01-19 Create README.MD
    Board Description + Images
2026-01-19 images
2026-01-19 moving things around
2026-01-19 changing file locations
2026-01-19 lock file (gets in the way)
2026-02-10 fix text on schematic
2026-02-12 global library.
    chicker done. next step is to merge all the rest into a global library
2026-02-12 midplate stuff + modify chicker silkscreen files
2026-02-12 some components files not working. checking a previous midplate branch
2026-02-12 midplate libraries fixed
2026-02-13 faceplate. broken.
2026-02-14 faceplate global files working
2026-02-14 added a title block
2026-02-23 siderakb mouse sensor PCB
2026-02-23 initial
2026-02-25 prod (gnd standoffs)
2026-02-25 gerbers for production
2026-02-25 no buttons broski
2026-02-26 mouse sensor bots libraries
    - footprints not done yet. shematics yes.
2026-02-26 3dmodels + footprints
    - one resistor unvalued + no footprint
2026-02-27 libraries and stuff
2026-02-27 mouse_sensorV1 prod done
2026-02-28 production files - working
    - modified board slightly, added 3d models, added part numbers for JLC
2026-03-02 can integration
2026-03-02 firmware update
    - blocking allocation by claude. 100Hz and 1kHz works, but 5kHz and above have too much memory allocation. will fix this eventually, but you can test with 1kHz.
2026-03-05 skid board schematic, need to check then do pcb
2026-03-08 update skidplate schematic with new imu
2026-03-11 idk even
2026-03-11 slightly better
2026-03-11 working, but patchy.
2026-03-15 updated skidplate schematic, need to add usb pd
2026-03-15 damping on hw pwm
2026-03-25 midplate pass through
    ethernet pass through
2026-03-25 white led fix
2026-04-01 3dmodels
2026-04-23 add usb pd and imu to midplate
2026-04-26 fix models
2026-04-26 wip some more
2026-04-26 wip faceplate 2.0 schematic
2026-04-28 add adafruit connector
2026-05-09 net names
2026-05-09 revert old faceplate PCB
2026-05-09 old-annotated schematic
2026-05-09 pcb updates
2026-05-10 ch;anges
2026-05-10 routed
2026-05-10 DRC Pass
2026-05-10 moved 2 pin connector
2026-05-10 file outputs
2026-05-11 midplate additions WIP
2026-05-16 skidplate
2026-05-16 skidplate, then realized its pointless
2026-05-17 skidplate done
2026-05-18 skidplate and midplate
2026-05-20 faceplatev2
2026-05-20 silk update
2026-05-20 production + fixing libraries
2026-05-25 workup
2026-05-25 file organization
2026-05-26 Update README.md
    committing before i lose the changes again
2026-05-26 Update README.md
    IMU add
2026-05-26 Update README.md symbol libraries
2026-05-27 16mhz
2026-05-27 update PCB
2026-05-27 baseplate v1.1
2026-05-28 fix paths
2026-05-28 baseplate zeroH standoffs
2026-05-28 zero height change to top.
2026-05-28 production files other side
2026-05-29 baseplate threaded insert change
2026-05-29 fix the threaded insert
2026-05-30 directory fixing
2026-06-01 netclass colours
2026-06-04 update faceplate documentation (almost done)
2026-06-09 Create LICENSE
2026-06-10 pcb colour
2026-06-10 solenoid active damping
2026-06-11 Rename LICENSE to LICENSE.txt
2026-06-11 Rename LICENSE.txt to LICENSE
2026-06-12 Update LICENSE
2026-06-16 updates for recommendations
2026-06-16 relevant code included
2026-06-17 discussion
2026-06-17 moving stuff around and videos
2026-06-29 robocup: push up fixes
2026-06-29 attempt
2026-06-29 final final
2026-06-29 final 2 before gta 6
2026-06-29 final final 3 final
2026-06-30 wip2
2026-06-30 extra high
2026-06-30 fix fault tree
2026-06-30 fix kick spam bugs
2026-06-30 galaxy brain codex fixes kicking again
2026-06-30 Fix kicking
2026-06-30 fix the world
